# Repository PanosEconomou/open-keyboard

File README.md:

# open-keyboard

I want a cool keyboard, and if I am going to spend so much money on a good one that someone else makes why not spend even more money for a worse one that I make?

## Journal

There is a [journal](./journal/02-layout-framing.md) here somewhere that documents the process.

## Acknowledgements

This project uses or is inspired by a lot of open-source tools, projects, and generous people who documented their work. Thank you so much!

### Tools & Software
- [Keyboard Layout Editor](https://www.keyboard-layout-editor.com) — Ian Prest's layout design tool, used for every layout iteration
- [QMK Firmware](https://qmk.fm) — the open-source "Quantum Mechanical Keyboard" firmware
- [FreeCAD](https://www.freecad.org) — open-source CAD used for the case design
- [KiCad](https://www.kicad.org) — open-source EDA used for the schematic and PCB
- [Blender](https://www.blender.org) — used for the renders
- [Plate & Case Builder](http://builder.swillkb.com) — swillkb's tool for generating plates/cases from a layout

### Open-Source Projects & Libraries
- [cubiq/OPK](https://github.com/cubiq/OPK) — open keycap profile / library (included as a submodule)
- [CadQuery](https://github.com/CadQuery/cadquery) — Python-based parametric CAD used for keycap generation
- [ai03-2725/MX_V2](https://github.com/ai03-2725/MX_V2) — MX switch KiCad component library
- [ebastler/marbastlib](https://github.com/ebastler/marbastlib) — recent MX hotswap footprint library (the one I went with)
- [kiswitch/kiswitch](https://github.com/kiswitch/kiswitch) — switch footprint library
- [olkb/olkb_parts](https://github.com/olkb/olkb_parts) — OLKB's CAD parts, referenced for case design
- [adafruit/Adafruit-Feather-RP2040-PCB](https://github.com/adafruit/Adafruit-Feather-RP2040-PCB) — RP2040 reference design
- [Unified Daughterboard standard](https://unified-daughterboard.github.io) — daughterboard spec for the gasket-mount design
- [network2501/planck](https://github.com/network2501/planck) — long-press shift layout idea

### Guides & Articles
- [Ruiqi Mao's Keyboard PCB Guide](https://github.com/ruiqimao/keyboard-pcb-guide) — invaluable PCB walkthrough
- [The Planck Constant](http://thedarnedestthing.com/planck%20constant) — thoughtful write-up on Planck layout design
- [Evan Travers — 40% keyboard layouts](https://evantravers.com/articles/2019/04/20/community-post-40-keyboard-layouts/) — community layout roundup
- [Designing Keycaps for Fun and Profit (kbd.news)](https://kbd.news/Designing-Keycaps-for-Fun-and-Profit-1775.html) — PBS keycap creator's guide
- [RP2040 Hardware Design Guide (Raspberry Pi)](https://pip-assets.raspberrypi.com/categories/814-rp2040/documents/RP-008279-DS-1-hardware-design-with-rp2040.pdf?disposition=inline)
- [How to make your PCB hotswappable](https://www.reddit.com/r/MechanicalKeyboards/comments/5a399o/guide_how_to_make_your_pcb_hotswappable/)

### Community Threads & Inspiration
- [r/olkb](https://www.reddit.com/r/olkb/) and [r/MechanicalKeyboards](https://www.reddit.com/r/MechanicalKeyboards/wiki/customkeyboards/) — the wikis, guides, and countless threads
- [Detailed guide to making a custom keyboard](https://www.reddit.com/r/MechanicalKeyboards/comments/4l0p41/guide_detailed_guide_to_making_a_custom_keyboard/)
- [Default Planck layout thread](https://www.reddit.com/r/MechanicalKeyboards/comments/4vs3iz/this_is_the_default_planck_layout/) and [Planck PCB options](https://www.reddit.com/r/olkb/comments/rh9r3n/planck_pcb_options/)
- [40s keycaps — where to begin](https://www.reddit.com/r/MechanicalKeyboards/comments/dzamyl/40s_keycaps_where_to_begin/)
- [Gasket mounting discussion (geekhack)](https://geekhack.org/index.php?topic=101731.0) and [switch LED orientation (geekhack)](https://geekhack.org/index.php?topic=72713.0)
- [Planck PCB rev 6 (imgur)](https://imgur.com/a/planck-pcb-rev-6-8gn3UQs) — component-margin reference
- Geonix and YMDK Air 40 builds that got me started (linked in the README)

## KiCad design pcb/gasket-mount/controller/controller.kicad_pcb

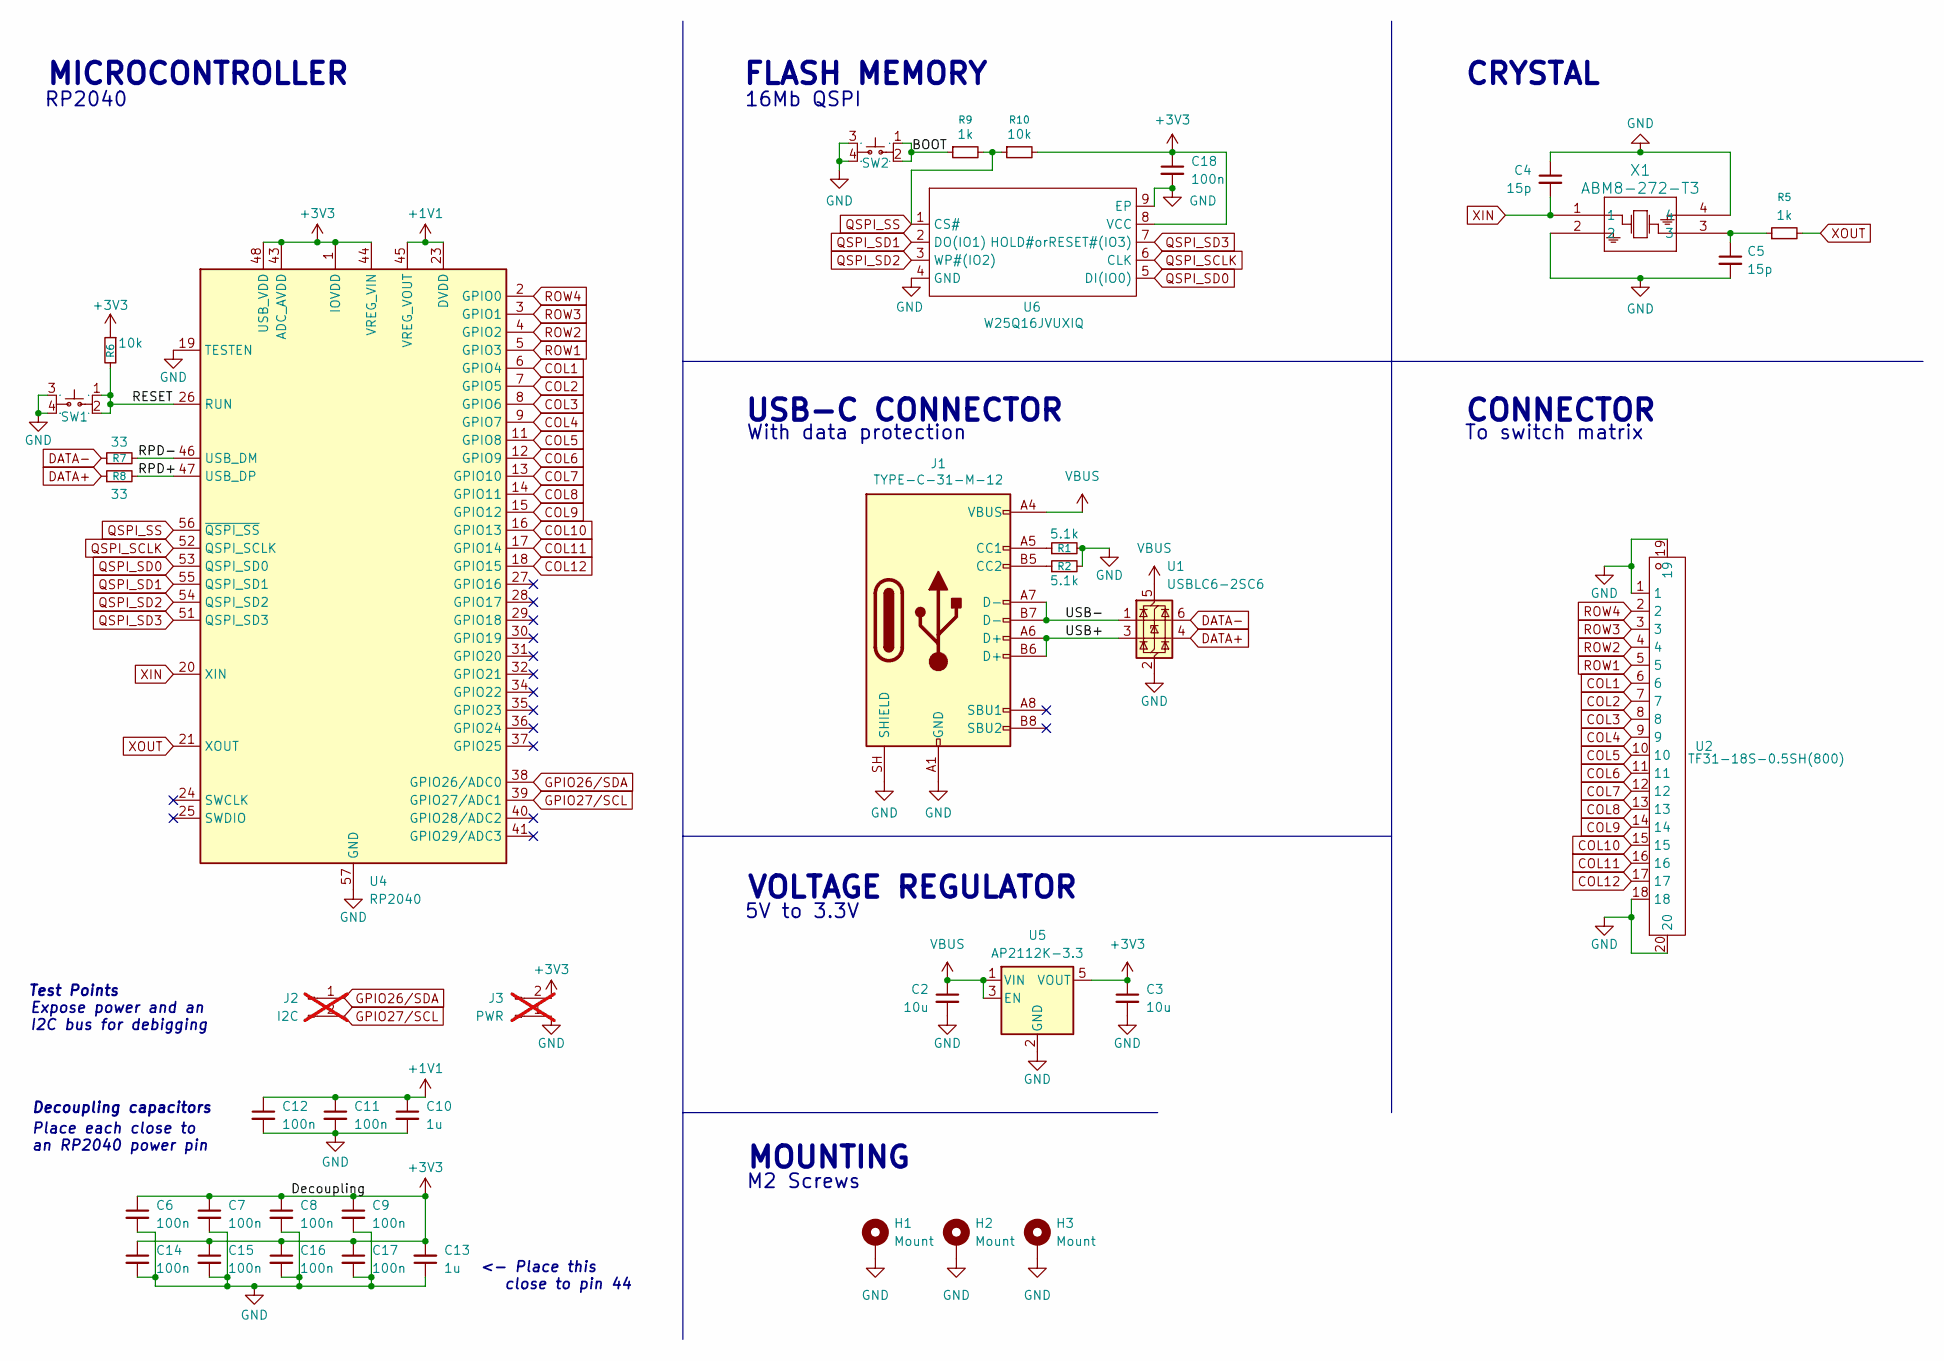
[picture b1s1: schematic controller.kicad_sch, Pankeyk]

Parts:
C2, C3: 10u; C_0603_1608Metric; LCSC C96446
C4, C5: 15p; C_0402_1005Metric; LCSC C1548
C6, C7, C8, C9, C11, C12, C14, C15, C16, C17, C18: 100n; C_0402_1005Metric; LCSC C1525
C10, C13: 1u; C_0402_1005Metric; LCSC C52923
H1, H2, H3: Mount; MountingHole_2.2mm_M2_ISO14580_Pad
J1: TYPE-C-31-M-12; USB_C_Receptacle_HRO_TYPE-C-31-M-12; LCSC TYPE-C-31-M-12
J2: I2C; PinHeader_1x02_P2.54mm_Vertical; not fitted
J3: PWR; PinHeader_1x02_P2.54mm_Vertical; not fitted
R1, R2: 5.1k; R_0402_1005Metric; LCSC C25905
R5, R9: 1k; R_0402_1005Metric; LCSC C11702
R6, R10: 10k; R_0402_1005Metric; LCSC C25744
R7, R8: 33; R_0402_1005Metric; LCSC C25105
SW1, SW2: SKRPAME010; KEY-SMD_4P-L4.2-W3.2-P2.20-LS4.6; Manufacturer Part SKRPAME010; LCSC C19724063
U1: USBLC6-2SC6; SOT-23-6; LCSC USBLC6-2SC6
U2: TF31-18S-0.5SH(800); FPC-SMD_18P-P0.50_TF31-18S-0.5SH-800; Manufacturer Part TF31-18S-0.5SH(800); LCSC Part Name 间距:0.5mm P数:18P 翻盖式 下接
U4: RP2040; QFN-56-1EP_7x7mm_P0.4mm_EP3.2x3.2mm; LCSC RP2040
U5: AP2112K-3.3; SOT-23-5; LCSC AP2112K-3.3
U6: W25Q16JVUXIQ; USON-8_L3.0-W2.0-P0.50-BL-EP; Manufacturer Part W25Q16JVUXIQ; LCSC C2843335
X1: ABM8-272-T3; Crystal_SMD_Abracon_ABM8G-4Pin_3.2x2.5mm; LCSC ABM8-272-T3

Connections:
+1V1: C10.1, C11.1, C12.1, U4.23 (DVDD), U4.45 (VREG_VOUT), U4.50 (DVDD)
+3V3: C3.1, C6.1, C7.1, C8.1, C9.1, C13.2, C14.1, C15.1, C16.1, C17.1, C18.1, J3.2, R6.1, R10.2, U4.1 (IOVDD), U4.10 (IOVDD), U4.22 (IOVDD), U4.33 (IOVDD), U4.42 (IOVDD), U4.43 (ADC_AVDD), U4.44 (VREG_VIN), U4.48 (USB_VDD), U4.49 (IOVDD), U5.5 (VOUT), U6.8 (VCC)
/BOOT: R9.1, SW2.1, SW2.2
/RESET: R6.2, SW1.1, SW1.2, U4.26 (RUN)
/RPD+: R8.2, U4.47 (USB_DP)
/RPD-: R7.2, U4.46 (USB_DM)
/USB+: J1.A6 (D+), J1.B6 (D+), U1.3 (I/O2)
/USB-: J1.A7 (D-), J1.B7 (D-), U1.1 (I/O1)
COL1: U2.6, U4.6 (GPIO4)
COL2: U2.7, U4.7 (GPIO5)
COL3: U2.8, U4.8 (GPIO6)
COL4: U2.9, U4.9 (GPIO7)
COL5: U2.10, U4.11 (GPIO8)
COL6: U2.11, U4.12 (GPIO9)
COL7: U2.12, U4.13 (GPIO10)
COL8: U2.13, U4.14 (GPIO11)
COL9: U2.14, U4.15 (GPIO12)
COL10: U2.15, U4.16 (GPIO13)
COL11: U2.16, U4.17 (GPIO14)
COL12: U2.17, U4.18 (GPIO15)
DATA+: R8.1, U1.4 (I/O2)
DATA-: R7.1, U1.6 (I/O1)
GND: C2.2, C3.2, C4.1, C5.2, C6.2, C7.2, C8.2, C9.2, C10.2, C11.2, C12.2, C13.1, C14.2, C15.2, C16.2, C17.2, C18.2, H1.1 (1_1), H2.1 (1_1), H3.1 (1_1), J1.A1 (GND), J1.A12 (GND), J1.B1 (GND), J1.B12 (GND), J1.SH (SHIELD), J3.1, R1.2, R2.2, SW1.3, SW1.4, SW2.3, SW2.4, U1.2 (GND), U2.1, U2.18, U2.19, U2.20, U4.19 (TESTEN), U4.57 (GND), U5.2 (GND), U6.4 (GND), U6.9 (EP), X1.2, X1.4
GPIO26/SDA: J2.1, U4.38 (GPIO26/ADC0)
GPIO27/SCL: J2.2, U4.39 (GPIO27/ADC1)
unnamed: C5.1, R5.1, X1.3
unnamed: J1.A5 (CC1), R1.1
unnamed: J1.B5 (CC2), R2.1
QSPI_SCLK: U4.52 (QSPI_SCLK), U6.6 (CLK)
QSPI_SD0: U4.53 (QSPI_SD0), U6.5 (DI(IO0))
QSPI_SD1: U4.55 (QSPI_SD1), U6.2 (DO(IO1))
QSPI_SD2: U4.54 (QSPI_SD2), U6.3 (WP#(IO2))
QSPI_SD3: U4.51 (QSPI_SD3), U6.7 (HOLD#orRESET#(IO3))
QSPI_SS: R9.2, R10.1, U4.56 (~QSPI_SS), U6.1 (CS#)
ROW1: U2.5, U4.5 (GPIO3)
ROW2: U2.4, U4.4 (GPIO2)
ROW3: U2.3, U4.3 (GPIO1)
ROW4: U2.2, U4.2 (GPIO0)
VBUS: C2.1, J1.A4 (VBUS), J1.A9 (VBUS), J1.B4 (VBUS), J1.B9 (VBUS), U1.5 (VBUS), U5.1 (VIN), U5.3 (EN)
XIN: C4.2, U4.20 (XIN), X1.1
XOUT: R5.2, U4.21 (XOUT)

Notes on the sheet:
USB-C CONNECTOR
RP2040
CONNECTOR
Decoupling capacitors
With data protection
MOUNTING
Place each close to an RP2040 power pin
M2 Screws
<- Place this close to pin 44
Expose power and an I2C bus for debigging
MICROCONTROLLER
16Mb QSPI
CRYSTAL
VOLTAGE REGULATOR
5V to 3.3V
FLASH MEMORY
Test Points
To switch matrix

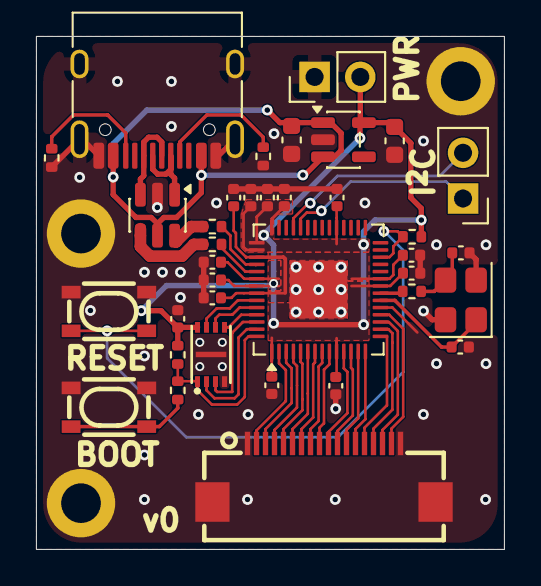
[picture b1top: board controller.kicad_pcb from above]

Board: 2 copper layers, 26.0 x 28.5 mm, 39 parts (0 on the bottom side), 41 nets.

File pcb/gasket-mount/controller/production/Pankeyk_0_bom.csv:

Designator,Footprint,Quantity,Value,LCSC Part #
"C10, C13",0402,2,1u,C52923
"C11, C12, C14, C15, C16, C17, C18, C6, C7, C8, C9",0402,11,100n,C1525
"C2, C3",0603,2,10u,C96446
"C4, C5",0402,2,15p,C1548
J1,USB_C_Receptacle_HRO_TYPE-C-31-M-12,1,TYPE-C-31-M-12,TYPE-C-31-M-12
"R1, R2",0402,2,5.1k,C25905
"R10, R6",0402,2,10k,C25744
"R5, R9",0402,2,1k,C11702
"R7, R8",0402,2,33,C25105
"SW1, SW2",KEY-SMD_4P-L4.2-W3.2-P2.20-LS4.6,2,SKRPAME010,C19724063
U1,SOT-23-6,1,USBLC6-2SC6,USBLC6-2SC6
U2,FPC-SMD_18P-P0.50_TF31-18S-0.5SH-800,1,TF31-18S-0.5SH(800),
U4,QFN-56-1EP_7x7mm_P0.4mm_EP3.2x3.2mm,1,RP2040,RP2040
U5,SOT-23-5,1,AP2112K-3.3,AP2112K-3.3
U6,USON-8_L3.0-W2.0-P0.50-BL-EP,1,W25Q16JVUXIQ,C2843335
X1,Crystal_SMD_Abracon_ABM8G-4Pin_3.2x2.5mm,1,ABM8-272-T3,ABM8-272-T3

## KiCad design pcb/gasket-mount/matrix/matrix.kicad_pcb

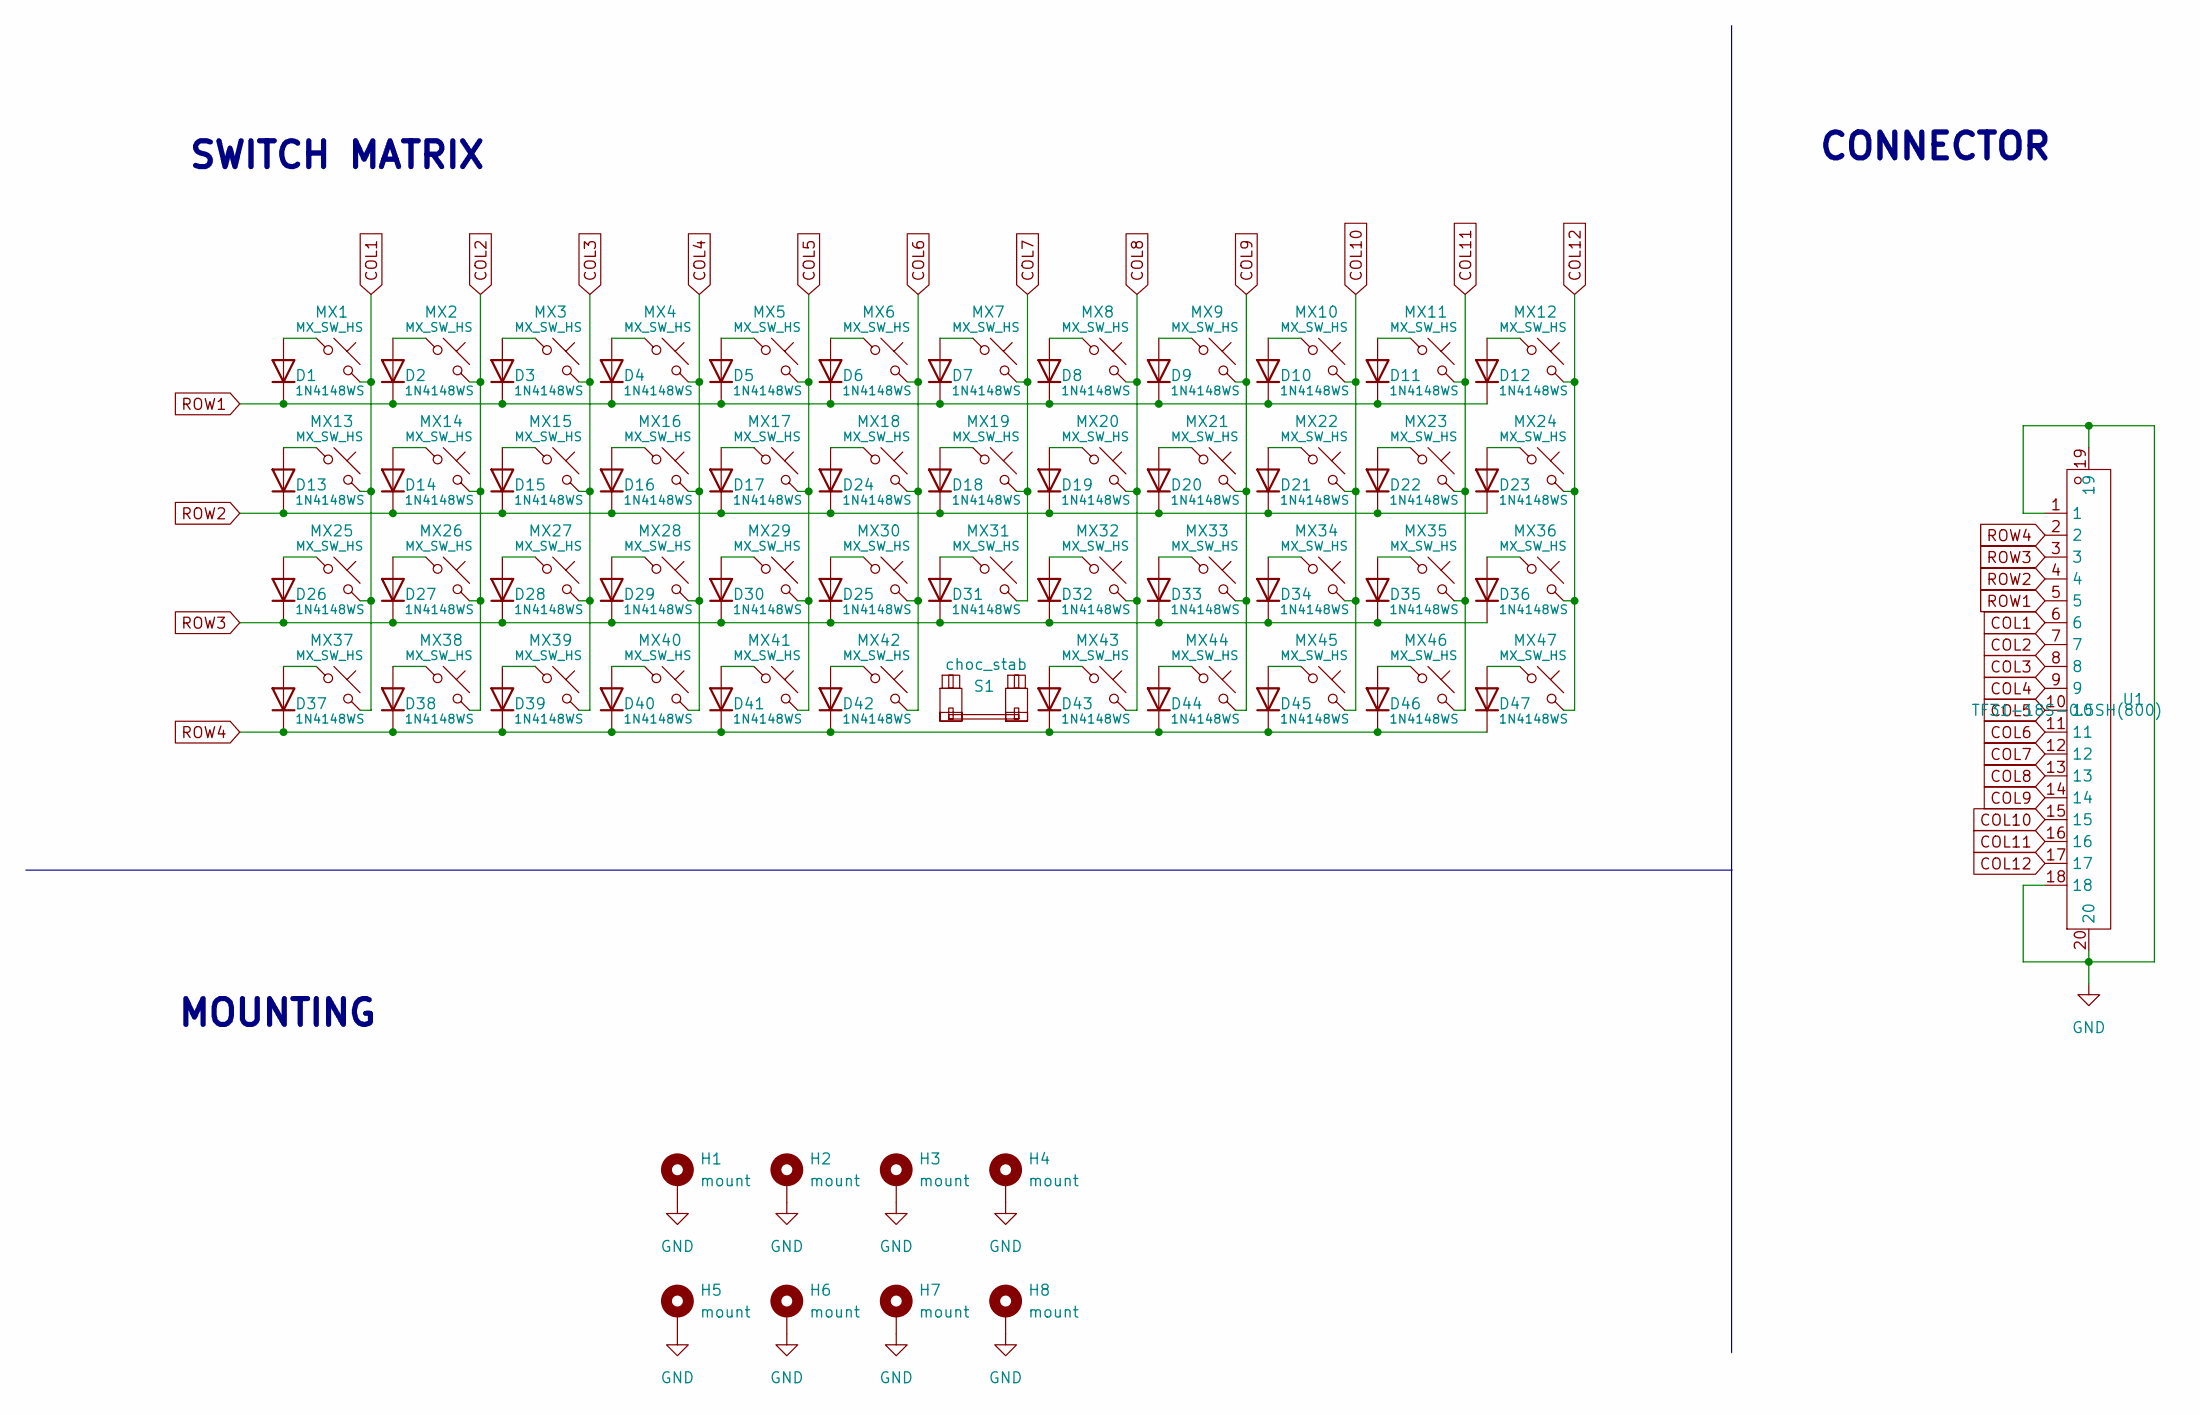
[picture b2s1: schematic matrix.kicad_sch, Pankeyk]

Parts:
D1, D2, D3, D4, D5, D6, D7, D8, D9, D10, D11, D12, D13, D14, D15, D16, D17, D18, D19, D20, D21, D22, D23, D24, D25, D26, D27, D28, D29, D30, D31, D32, D33, D34, D35, D36, D37, D38, D39, D40, D41, D42, D43, D44, D45, D46, D47: 1N4148WS; D_SOD-323; LCSC 1N4148WS
H1, H2, H3, H4, H5, H6, H7, H8: mount; MountingHole_2.2mm_M2_Pad_TopBottom
MX1, MX2, MX3, MX4, MX5, MX6, MX7, MX8, MX9, MX10, MX11, MX12, MX13, MX14, MX15, MX16, MX17, MX18, MX19, MX20, MX21, MX22, MX23, MX24, MX25, MX26, MX27, MX28, MX29, MX30, MX31, MX32, MX33, MX34, MX35, MX36, MX37, MX38, MX39, MX40, MX41, MX42, MX43, MX44, MX45, MX46, MX47: MX_SW_HS; SW_MX_HS_CPG151101S11_1u; LCSC CPG151101S11-2
S1: choc_stab; STAB_choc_2u
U1: TF31-18S-0.5SH(800); FPC-SMD_18P-P0.50_TF31-18S-0.5SH-800; Manufacturer Part TF31-18S-0.5SH(800); LCSC Part Name 间距:0.5mm P数:18P 翻盖式 下接

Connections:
COL1: MX1.2, MX13.2, MX25.2, MX37.2, U1.6
COL2: MX2.2, MX14.2, MX26.2, MX38.2, U1.7
COL3: MX3.2, MX15.2, MX27.2, MX39.2, U1.8
COL4: MX4.2, MX16.2, MX28.2, MX40.2, U1.9
COL5: MX5.2, MX17.2, MX29.2, MX41.2, U1.10
COL6: MX6.2, MX18.2, MX30.2, MX42.2, U1.11
COL7: MX7.2, MX19.2, MX31.2, U1.12
COL8: MX8.2, MX20.2, MX32.2, MX43.2, U1.13
COL9: MX9.2, MX21.2, MX33.2, MX44.2, U1.14
COL10: MX10.2, MX22.2, MX34.2, MX45.2, U1.15
COL11: MX11.2, MX23.2, MX35.2, MX46.2, U1.16
COL12: MX12.2, MX24.2, MX36.2, MX47.2, U1.17
GND: H1.1 (1_1), H2.1 (1_1), H3.1 (1_1), H4.1 (1_1), H5.1 (1_1), H6.1 (1_1), H7.1 (1_1), H8.1 (1_1), U1.1, U1.18, U1.19, U1.20
unnamed: D1.2 (A), MX1.1
unnamed: D2.2 (A), MX2.1
unnamed: D3.2 (A), MX3.1
unnamed: D4.2 (A), MX4.1
unnamed: D5.2 (A), MX5.1
unnamed: D6.2 (A), MX6.1
unnamed: D7.2 (A), MX7.1
unnamed: D8.2 (A), MX8.1
unnamed: D9.2 (A), MX9.1
unnamed: D10.2 (A), MX10.1
unnamed: D11.2 (A), MX11.1
unnamed: D12.2 (A), MX12.1
unnamed: D13.2 (A), MX13.1
unnamed: D14.2 (A), MX14.1
unnamed: D15.2 (A), MX15.1
unnamed: D16.2 (A), MX16.1
unnamed: D17.2 (A), MX17.1
unnamed: D18.2 (A), MX19.1
unnamed: D19.2 (A), MX20.1
unnamed: D20.2 (A), MX21.1
unnamed: D21.2 (A), MX22.1
unnamed: D22.2 (A), MX23.1
unnamed: D23.2 (A), MX24.1
unnamed: D24.2 (A), MX18.1
unnamed: D25.2 (A), MX30.1
unnamed: D26.2 (A), MX25.1
unnamed: D27.2 (A), MX26.1
unnamed: D28.2 (A), MX27.1
unnamed: D29.2 (A), MX28.1
unnamed: D30.2 (A), MX29.1
unnamed: D31.2 (A), MX31.1
unnamed: D32.2 (A), MX32.1
unnamed: D33.2 (A), MX33.1
unnamed: D34.2 (A), MX34.1
unnamed: D35.2 (A), MX35.1
unnamed: D36.2 (A), MX36.1
unnamed: D37.2 (A), MX37.1
unnamed: D38.2 (A), MX38.1
unnamed: D39.2 (A), MX39.1
unnamed: D40.2 (A), MX40.1
unnamed: D41.2 (A), MX41.1
unnamed: D42.2 (A), MX42.1
unnamed: D43.2 (A), MX43.1
unnamed: D44.2 (A), MX44.1
unnamed: D45.2 (A), MX45.1
unnamed: D46.2 (A), MX46.1
unnamed: D47.2 (A), MX47.1
ROW1: D1.1 (K), D2.1 (K), D3.1 (K), D4.1 (K), D5.1 (K), D6.1 (K), D7.1 (K), D8.1 (K), D9.1 (K), D10.1 (K), D11.1 (K), D12.1 (K), U1.5
ROW2: D13.1 (K), D14.1 (K), D15.1 (K), D16.1 (K), D17.1 (K), D18.1 (K), D19.1 (K), D20.1 (K), D21.1 (K), D22.1 (K), D23.1 (K), D24.1 (K), U1.4
ROW3: D25.1 (K), D26.1 (K), D27.1 (K), D28.1 (K), D29.1 (K), D30.1 (K), D31.1 (K), D32.1 (K), D33.1 (K), D34.1 (K), D35.1 (K), D36.1 (K), U1.3
ROW4: D37.1 (K), D38.1 (K), D39.1 (K), D40.1 (K), D41.1 (K), D42.1 (K), D43.1 (K), D44.1 (K), D45.1 (K), D46.1 (K), D47.1 (K), U1.2

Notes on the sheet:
CONNECTOR
MOUNTING
SWITCH MATRIX

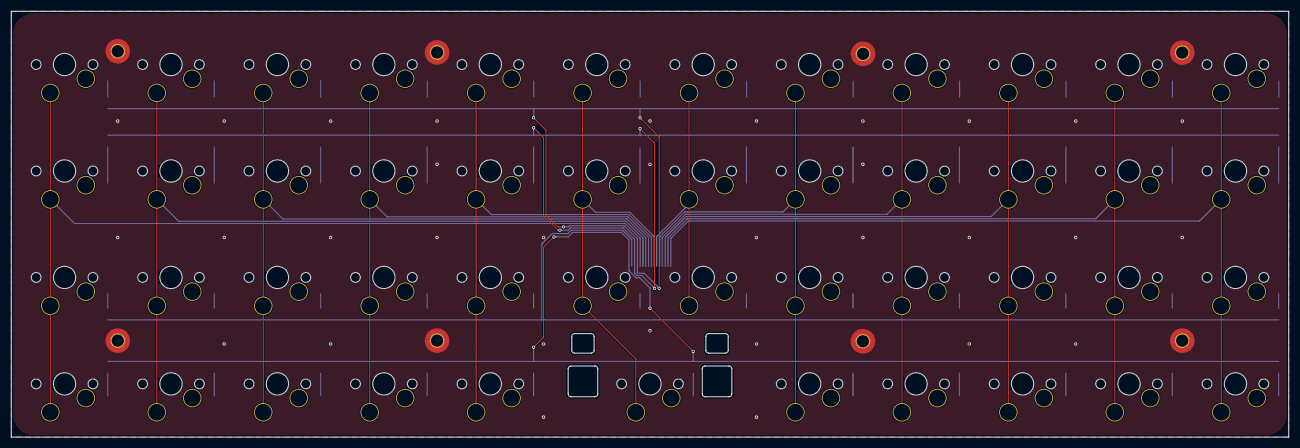
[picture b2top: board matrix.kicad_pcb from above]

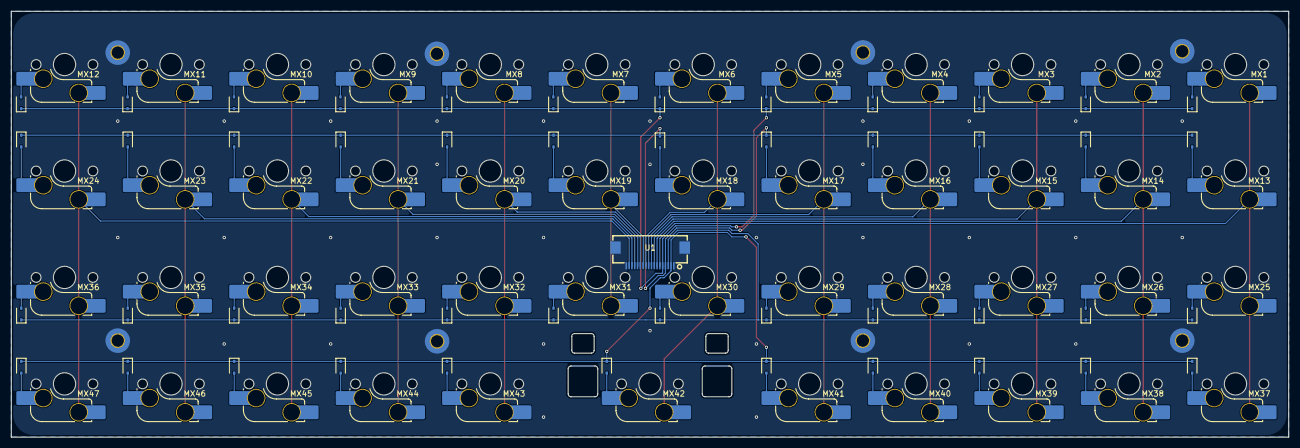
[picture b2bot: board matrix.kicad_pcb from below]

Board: 2 copper layers, 228.6 x 76.2 mm, 104 parts (95 on the bottom side), 64 nets.

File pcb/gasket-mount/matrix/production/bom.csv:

Designator,Footprint,Quantity,Value,LCSC Part #
"D1, D10, D11, D12, D13, D14, D15, D16, D17, D18, D19, D2, D20, D21, D22, D23, D24, D25, D26, D27, D28, D29, D3, D30, D31, D32, D33, D34, D35, D36, D37, D38, D39, D4, D40, D41, D42, D43, D44, D45, D46, D47, D5, D6, D7, D8, D9",D_SOD-323,47,1N4148WS,1N4148WS
"MX1, MX10, MX11, MX12, MX13, MX14, MX15, MX16, MX17, MX18, MX19, MX2, MX20, MX21, MX22, MX23, MX24, MX25, MX26, MX27, MX28, MX29, MX3, MX30, MX31, MX32, MX33, MX34, MX35, MX36, MX37, MX38, MX39, MX4, MX40, MX41, MX42, MX43, MX44, MX45, MX46, MX47, MX5, MX6, MX7, MX8, MX9",SW_MX_HS_CPG151101S11_1u,47,MX_SW_HS,CPG151101S11-2
U1,FPC-SMD_18P-P0.50_TF31-18S-0.5SH-800,1,TF31-18S-0.5SH(800),

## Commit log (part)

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2026-05-19 some resources
2026-05-19 Initial layout tries
2026-05-19 cleanup
2026-05-19 some latex suggestions
2026-05-19 layout with some thinking
2026-05-19 Document keyboard layout designs with images
    Added detailed descriptions and images for various keyboard layouts including Base, Number, Navigation, and Function modes.
2026-05-19 more resources
2026-05-20 new schematic
2026-05-20 Squashed 'pcb/component-libraries/MX_V2/' content from commit 0b379ee
    git-subtree-dir: pcb/component-libraries/MX_V2
    git-subtree-split: 0b379eebbeb66c7fd6e82e400b47958ad695614e
2026-05-20 First pcb schematic
2026-05-20 ignore temporary kicad files
2026-05-20 subtle thigns
2026-05-21 crystals
2026-05-21 schematic version 1
2026-05-22 woopsie typo
2026-05-22 centering pcb
2026-05-23 bottom case rev 1 and pcb updates
2026-05-24 pdb v1
2026-05-24 pcb v1
2026-05-25 Minor placement changes and mates
2026-05-29 pcb BOM updates
2026-05-29 case asseembly
2026-06-02 pcb updates
2026-06-02 case restart for gasket
2026-06-06 organization
2026-06-07 bottom case
2026-06-07 gasket mount
2026-06-08 top plate with screws
2026-06-09 CNC Training and daughterboard updates
2026-06-23 ok so time to make a daughter board
